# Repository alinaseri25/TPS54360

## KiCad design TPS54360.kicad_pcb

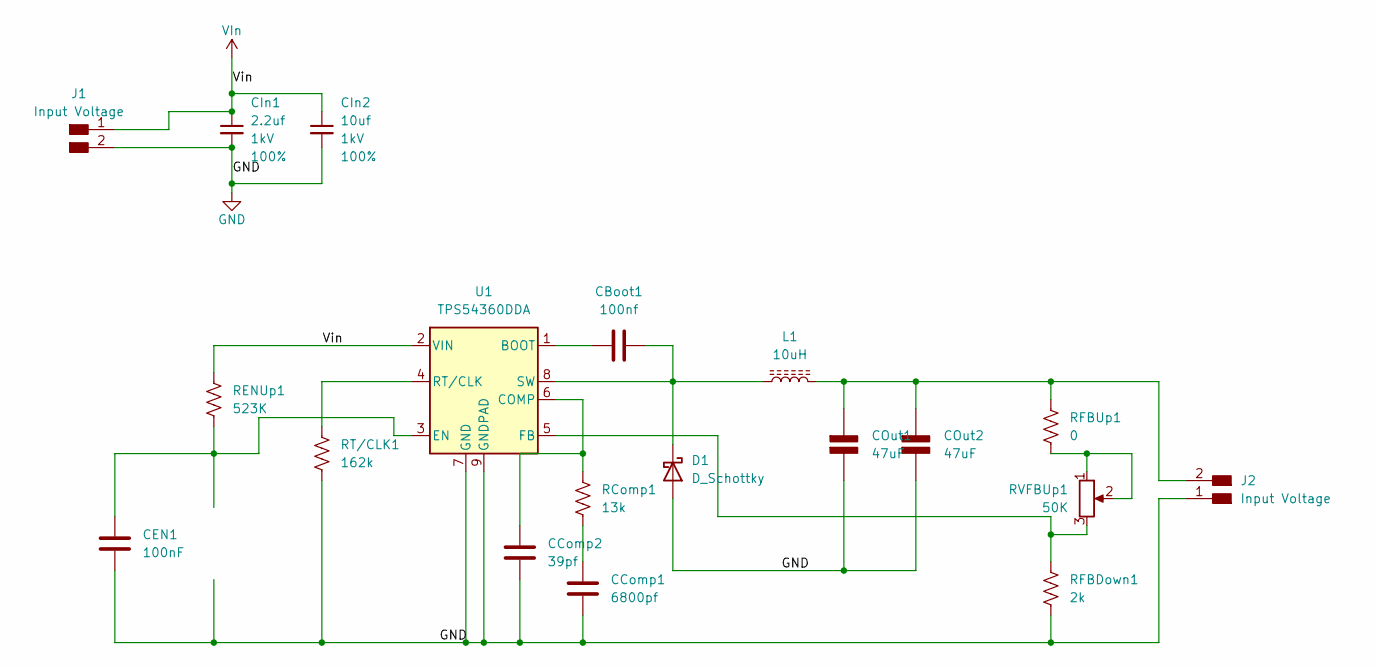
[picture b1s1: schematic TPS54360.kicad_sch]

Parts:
CBoot1: 100nf; C_0201_0603Metric
CComp1: 6800pf; C_0201_0603Metric
CComp2: 39pf; C_0201_0603Metric
CEN1: 100nF; C_0201_0603Metric
CIn1: 2.2uf; C_1206_3216Metric; Voltage 1kV; Tolerance 100%
CIn2: 10uf; C_1206_3216Metric; Voltage 1kV; Tolerance 100%
COut1, COut2: 47uF; C_0201_0603Metric; Rating V
D1: D_Schottky; D_SMB
J1, J2: Input Voltage; PinHeader_1x02_P2.54mm_Vertical
L1: 10uH; L_TracoPower_TCK-047_5.2x5.8mm
RComp1: 13k; C_0201_0603Metric
RENUp1: 523K; R_1206_3216Metric
RFBDown1: 2k; R_0201_0603Metric
RFBUp1: 0; R_0201_0603Metric
RT/CLK1: 162k; C_0201_0603Metric
RVFBUp1: 50K; Potentiometer_Bourns_3296W_Vertical
U1: TPS54360DDA; TI_SO-PowerPAD-8_ThermalVias

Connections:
GND: CComp1.2, CComp2.2, CEN1.2, CIn1.2, CIn2.2, COut1.2 (-), COut2.2 (-), D1.2 (A), J1.2, J2.1, RFBDown1.1, RT/CLK1.1, U1.7 (GND), U1.9 (GNDPAD)
unnamed: CComp1.1, RComp1.1
unnamed: COut1.1 (+), COut2.1 (+), J2.2, L1.2, RFBUp1.2
unnamed: CBoot1.1, D1.1 (K), L1.1, U1.8 (SW)
unnamed: RFBUp1.1, RVFBUp1.1, RVFBUp1.2
unnamed: CBoot1.2, U1.1 (BOOT)
unnamed: CComp2.1, RComp1.2, U1.6 (COMP)
unnamed: CEN1.1, RENUp1.1, U1.3 (EN)
unnamed: RFBDown1.2, RVFBUp1.3, U1.5 (FB)
unnamed: RT/CLK1.2, U1.4 (RT/CLK)
VIn: CIn1.1, CIn2.1, J1.1, RENUp1.2, U1.2 (VIN)

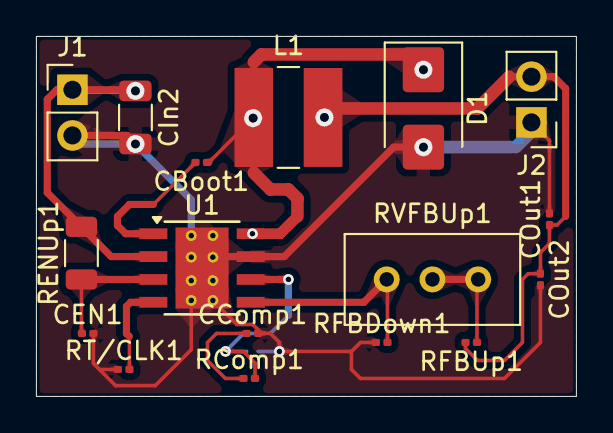
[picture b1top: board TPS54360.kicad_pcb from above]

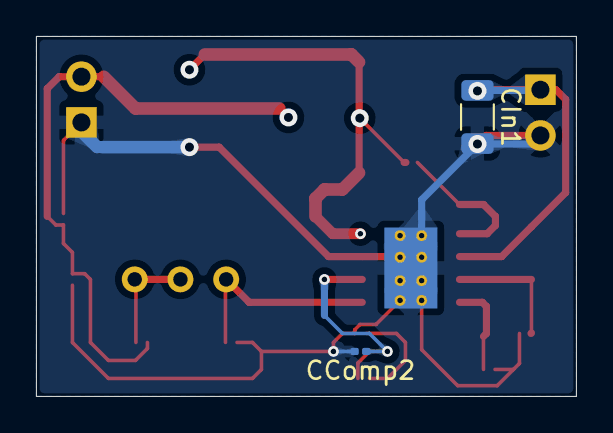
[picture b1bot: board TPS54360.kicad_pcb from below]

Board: 2 copper layers, 30.0 x 20.0 mm, 19 parts (2 on the bottom side), 11 nets.

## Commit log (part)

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2025-09-01 initialize
